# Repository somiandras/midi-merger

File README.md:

# Midi Merge Box

My embedded 🦀 Rust learning project: 2 in, 5 out MIDI merge box based
on a Raspberry Pico board.

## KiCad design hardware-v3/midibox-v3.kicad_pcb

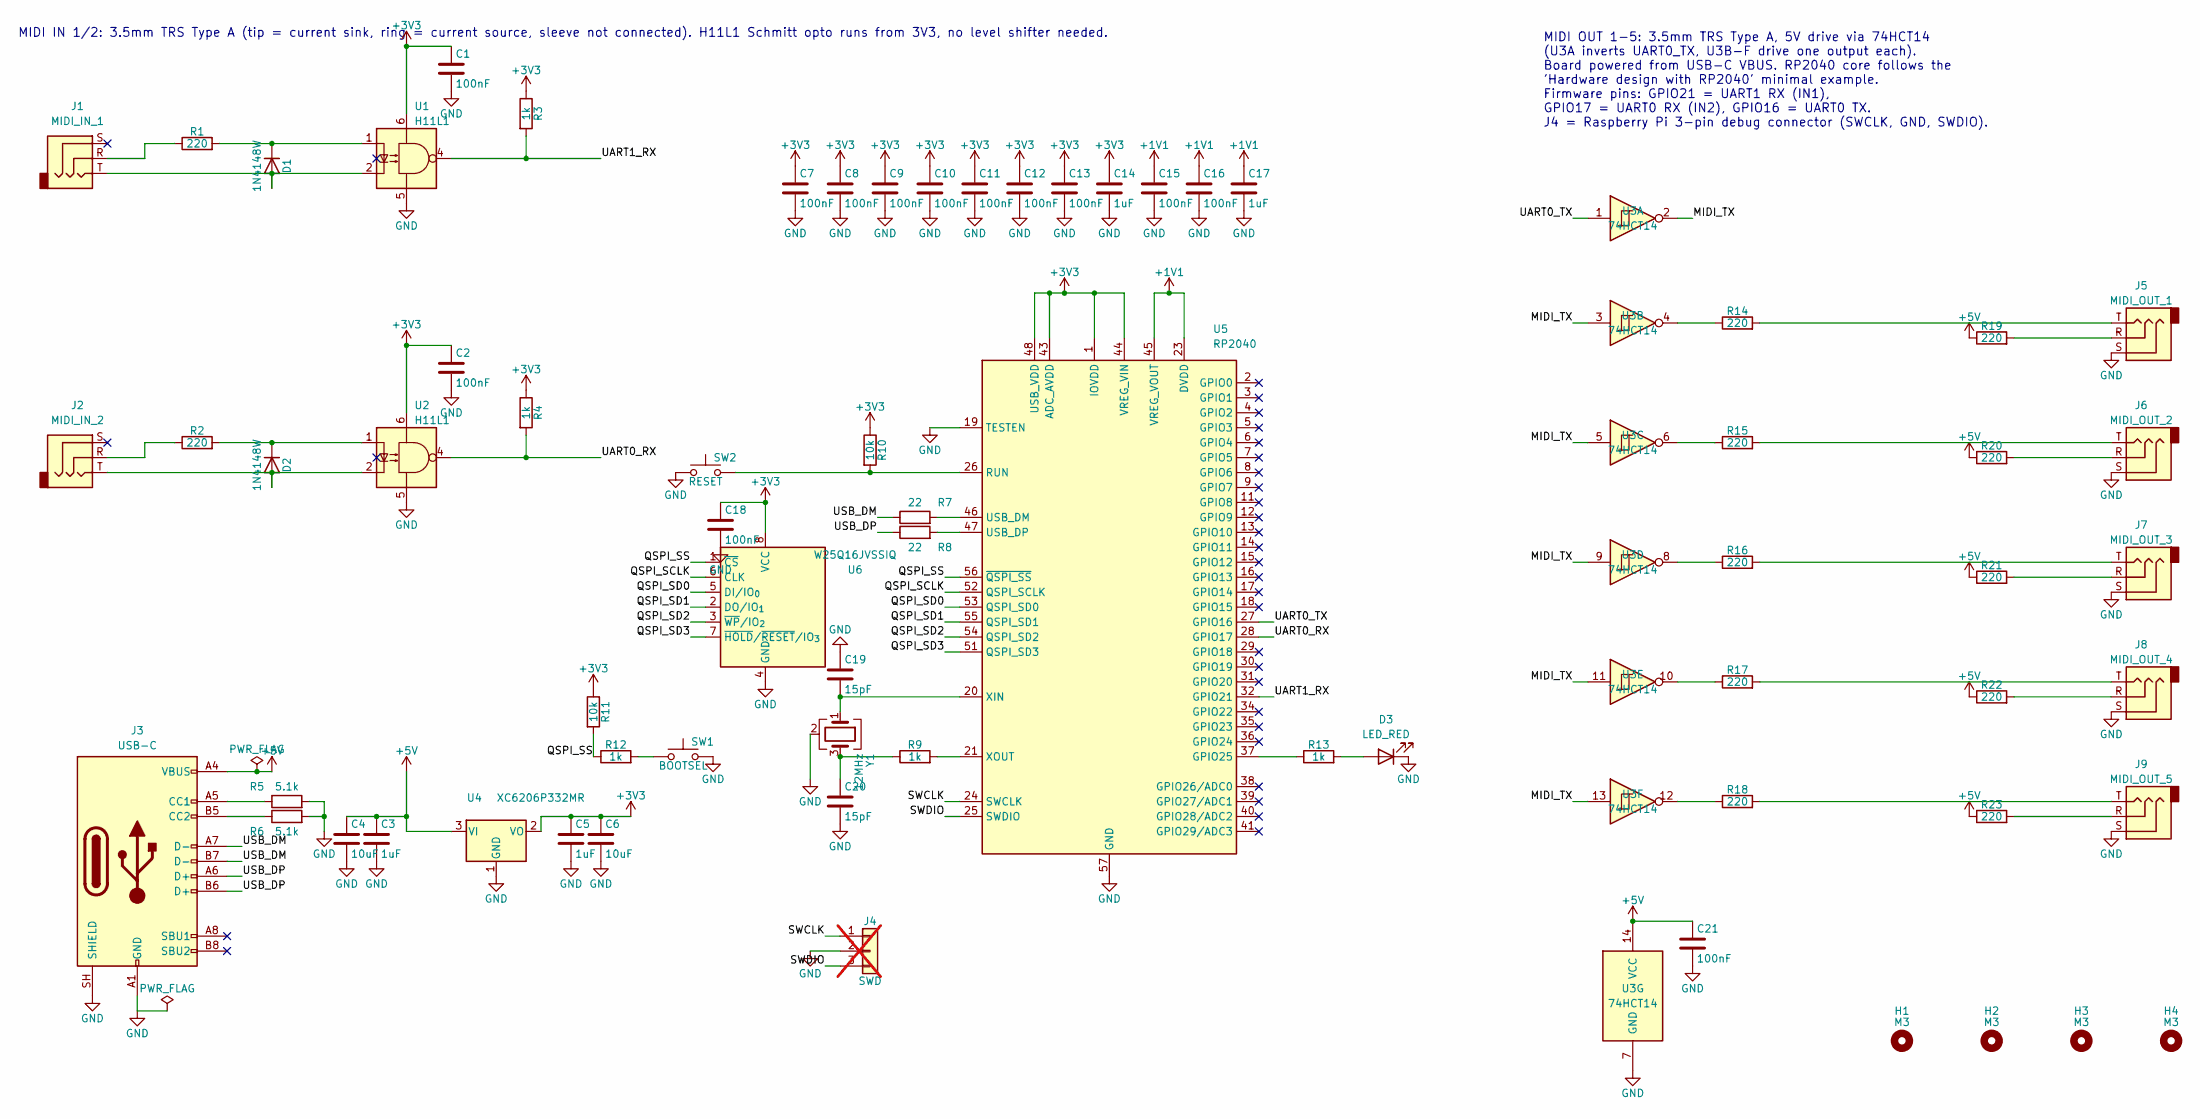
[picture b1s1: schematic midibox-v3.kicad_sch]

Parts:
C1, C2, C7, C8, C9, C10, C11, C12, C13, C15, C16, C18, C21: 100nF; C_0402_1005Metric; LCSC C1525
C3, C5, C14, C17: 1uF; C_0402_1005Metric; LCSC C52923
C4, C6: 10uF; C_0805_2012Metric; LCSC C15850
C19, C20: 15pF; C_0402_1005Metric; LCSC C1548
D1, D2: 1N4148W; D_SOD-123; LCSC C81598
D3: LED_RED; LED_0603_1608Metric; MPN KT-0603R; LCSC C2286
H1, H2, H3, H4: M3; MountingHole_3.2mm_M3
J1: MIDI_IN_1; PJ-3136-B_TRS; MPN PJ-3136-B
J2: MIDI_IN_2; PJ-3136-B_TRS; MPN PJ-3136-B
J3: USB-C; USB_C_Receptacle_HRO_TYPE-C-31-M-12; MPN TYPE-C-31-M-12; LCSC C165948
J4: SWD; PinHeader_1x03_P2.54mm_Vertical; not fitted
J5: MIDI_OUT_1; PJ-3136-B_TRS; MPN PJ-3136-B
J6: MIDI_OUT_2; PJ-3136-B_TRS; MPN PJ-3136-B
J7: MIDI_OUT_3; PJ-3136-B_TRS; MPN PJ-3136-B
J8: MIDI_OUT_4; PJ-3136-B_TRS; MPN PJ-3136-B
J9: MIDI_OUT_5; PJ-3136-B_TRS; MPN PJ-3136-B
R1, R2, R14, R15, R16, R17, R18, R19, R20, R21, R22, R23: 220; R_0402_1005Metric; LCSC C25091
R3, R4, R9, R12, R13: 1k; R_0402_1005Metric; LCSC C11702
R5, R6: 5.1k; R_0402_1005Metric; LCSC C25905
R7, R8: 22; R_0402_1005Metric; LCSC C25092
R10, R11: 10k; R_0402_1005Metric; LCSC C25744
SW1: BOOTSEL; SW_Push_1P1T_XKB_TS-1187A; MPN TS-1187A-B-A-B; LCSC C318884
SW2: RESET; SW_Push_1P1T_XKB_TS-1187A; MPN TS-1187A-B-A-B; LCSC C318884
U1, U2: H11L1; SMDIP-6_W9.53mm; MPN H11L1SR2M; LCSC C20082
U3: 74HCT14; SOIC-14_3.9x8.7mm_P1.27mm; MPN SN74HCT14DR; LCSC C6769
U4: XC6206P332MR; SOT-23-3; MPN XC6206P332MR-G; LCSC C5446
U5: RP2040; QFN-56-1EP_7x7mm_P0.4mm_EP3.2x3.2mm; MPN RP2040; LCSC C2040
U6: W25Q16JVSSIQ; SOIC-8_5.3x5.3mm_P1.27mm; MPN W25Q16JVSSIQ; LCSC C131025
Y1: 12MHz; Crystal_SMD_3225-4Pin_3.2x2.5mm; MPN ABM8-272-T3; LCSC C20625731

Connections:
+1V1: C15.1, C16.1, C17.1, U5.23 (DVDD), U5.45 (VREG_VOUT), U5.50 (DVDD)
+3V3: C1.1, C2.1, C5.1, C6.1, C7.1, C8.1, C9.1, C10.1, C11.1, C12.1, C13.1, C14.1, C18.1, R3.1, R4.1, R10.1, R11.1, U1.6, U2.6, U4.2 (VO), U5.1 (IOVDD), U5.10 (IOVDD), U5.22 (IOVDD), U5.33 (IOVDD), U5.42 (IOVDD), U5.43 (ADC_AVDD), U5.44 (VREG_VIN), U5.48 (USB_VDD), U5.49 (IOVDD), U6.8 (VCC)
+5V: C3.1, C4.1, C21.1, J3.A4 (VBUS), J3.A9 (VBUS), J3.B4 (VBUS), J3.B9 (VBUS), R19.1, R20.1, R21.1, R22.1, R23.1, U3.14 (VCC), U4.3 (VI)
/MIDI_TX: U3.2, U3.3, U3.5, U3.9, U3.11, U3.13
/QSPI_SCLK: U5.52 (QSPI_SCLK), U6.6 (CLK)
/QSPI_SD0: U5.53 (QSPI_SD0), U6.5 (DI/IO_{0})
/QSPI_SD1: U5.55 (QSPI_SD1), U6.2 (DO/IO_{1})
/QSPI_SD2: U5.54 (QSPI_SD2), U6.3 (~WP/IO_{2})
/QSPI_SD3: U5.51 (QSPI_SD3), U6.7 (~HOLD/~RESET/IO_{3})
/QSPI_SS: R11.2, R12.1, U5.56 (~QSPI_SS), U6.1 (~CS)
/SWCLK: J4.1, U5.24 (SWCLK)
/SWDIO: J4.3, U5.25 (SWDIO)
/UART0_RX: R4.2, U2.4, U5.28 (GPIO17)
/UART0_TX: U3.1, U5.27 (GPIO16)
/UART1_RX: R3.2, U1.4, U5.32 (GPIO21)
/USB_DM: J3.A7 (D-), J3.B7 (D-), R7.1
/USB_DP: J3.A6 (D+), J3.B6 (D+), R8.1
GND: C1.2, C2.2, C3.2, C4.2, C5.2, C6.2, C7.2, C8.2, C9.2, C10.2, C11.2, C12.2, C13.2, C14.2, C15.2, C16.2, C17.2, C18.2, C19.1, C20.2, C21.2, D3.1 (K), J3.A1 (GND), J3.A12 (GND), J3.B1 (GND), J3.B12 (GND), J3.SH (SHIELD), J4.2, J5.S, J6.S, J7.S, J8.S, J9.S, R5.2, R6.2, SW1.2, SW2.1, U1.5, U2.5, U3.7 (GND), U4.1 (GND), U5.19 (TESTEN), U5.57 (GND), U6.4 (GND), Y1.2 (G), Y1.4 (G)
unnamed: C20.1, R9.1, Y1.3
unnamed: D1.2 (A), J1.T, U1.2
unnamed: D1.1 (K), R1.2, U1.1
unnamed: D2.2 (A), J2.T, U2.2
unnamed: D2.1 (K), R2.2, U2.1
unnamed: D3.2 (A), R13.2
unnamed: J1.R, R1.1
unnamed: J2.R, R2.1
unnamed: J3.A5 (CC1), R5.1
unnamed: J3.B5 (CC2), R6.1
unnamed: J5.R, R19.2
unnamed: J5.T, R14.2
unnamed: J6.R, R20.2
unnamed: J6.T, R15.2
unnamed: J7.R, R21.2
unnamed: J7.T, R16.2
unnamed: J8.R, R22.2
unnamed: J8.T, R17.2
unnamed: J9.R, R23.2
unnamed: J9.T, R18.2
unnamed: R12.2, SW1.1
unnamed: R14.1, U3.4
unnamed: R15.1, U3.6
unnamed: R16.1, U3.8
unnamed: R17.1, U3.10
unnamed: R18.1, U3.12
unnamed: R13.1, U5.37 (GPIO25)
unnamed: R10.2, SW2.2, U5.26 (RUN)
unnamed: R7.2, U5.46 (USB_DM)
unnamed: R8.2, U5.47 (USB_DP)
unnamed: C19.2, U5.20 (XIN), Y1.1
unnamed: R9.2, U5.21 (XOUT)

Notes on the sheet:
MIDI IN 1/2: 3.5mm TRS Type A (tip = current sink, ring = current source, sleeve not connected). H11L1 Schmitt opto runs from 3V3, no level shifter needed.
MIDI OUT 1-5: 3.5mm TRS Type A, 5V drive via 74HCT14 (U3A inverts UART0_TX, U3B-F drive one output each). Board powered from USB-C VBUS. RP2040 core follows the 'Hardware design with RP2040' minimal example. Firmware pins: GPIO21 = UART1 RX (IN1), GPIO17 = UART0 RX (IN2), GPIO16 = UART0 TX. J4 = Ra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

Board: 2 copper layers, 69 parts (0 on the bottom side), 50 nets, no tracks yet.

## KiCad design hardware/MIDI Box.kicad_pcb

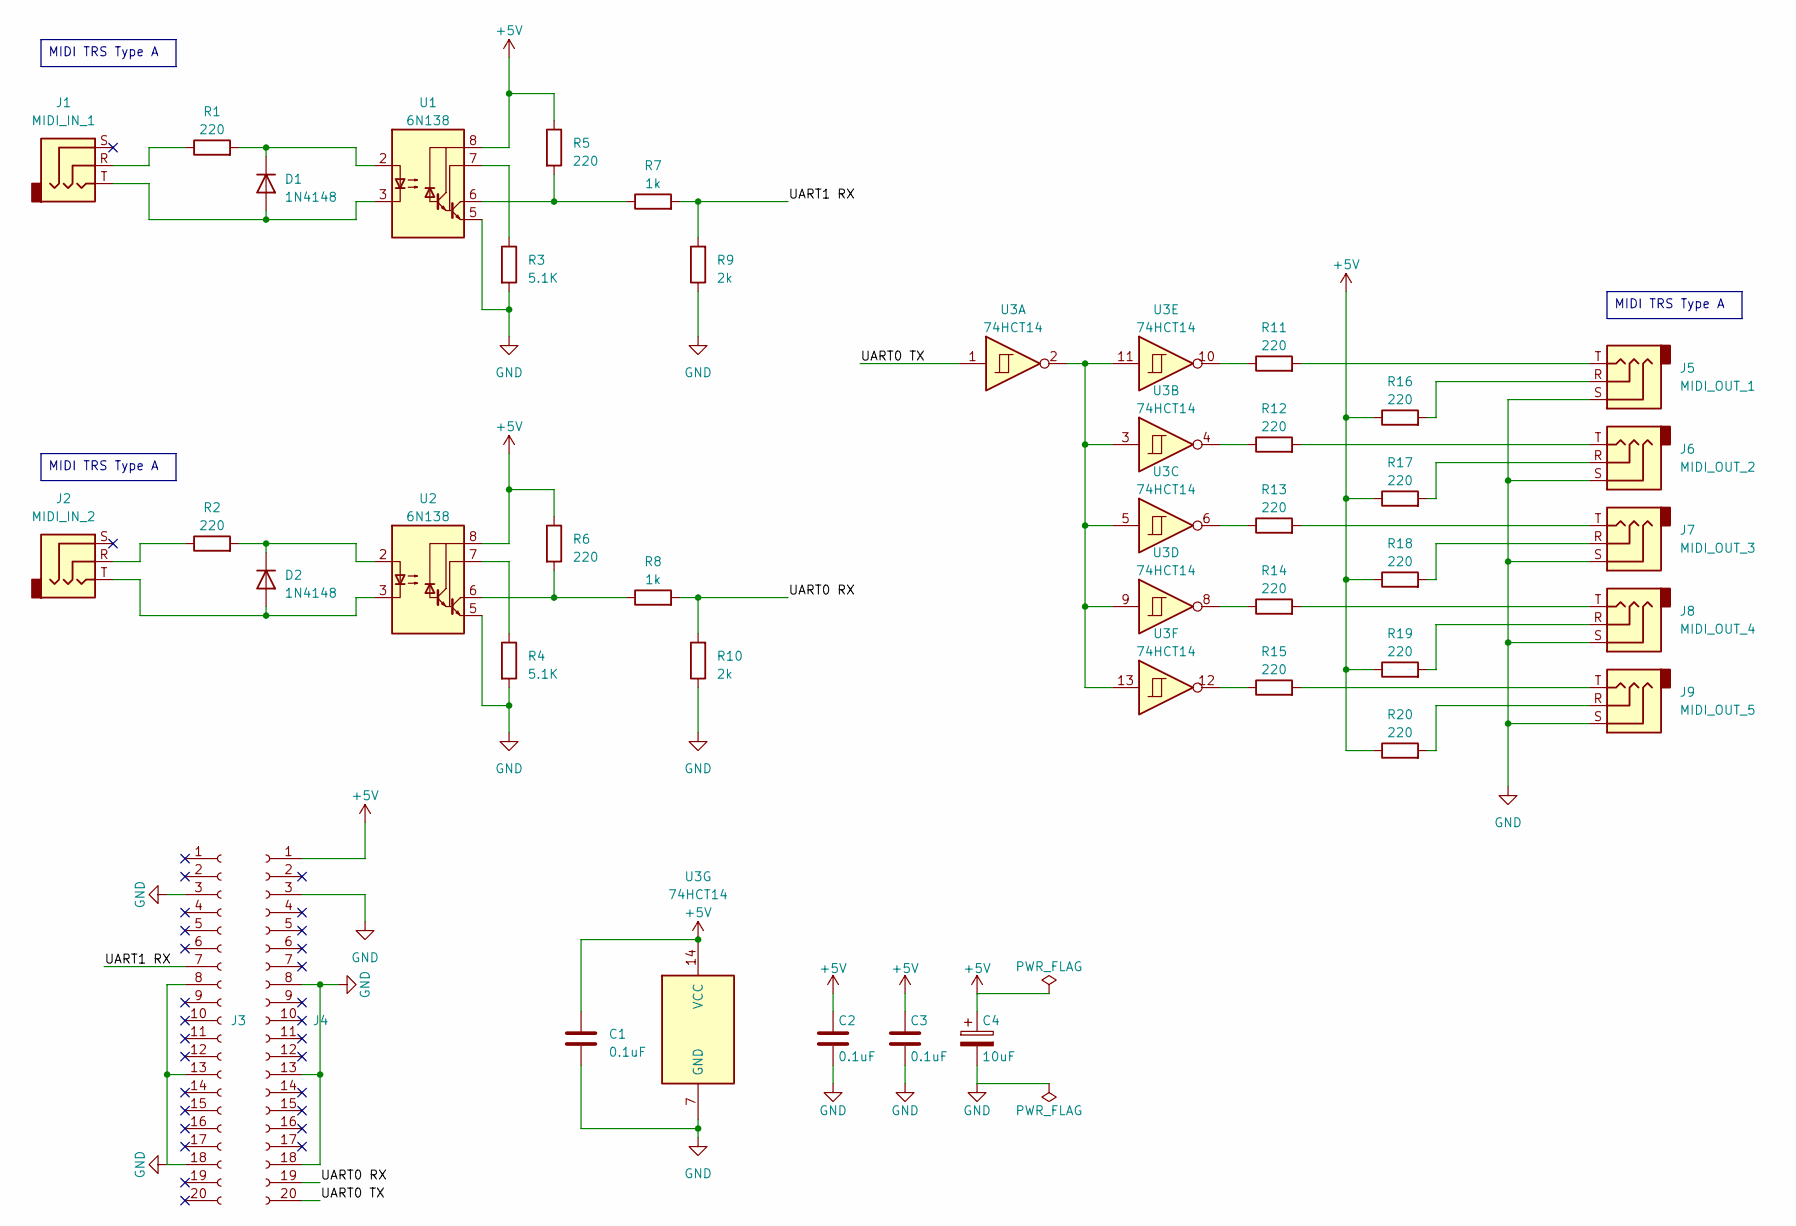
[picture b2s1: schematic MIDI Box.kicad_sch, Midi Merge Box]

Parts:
C1, C2, C3: 0.1uF; C_Disc_D3.4mm_W2.1mm_P2.50mm
C4: 10uF; CP_Radial_D5.0mm_P2.00mm
D1, D2: 1N4148; D_T-1_P5.08mm_Horizontal
J1: MIDI_IN_1; Audio Jack PJ-3136-B
J2: MIDI_IN_2; Audio Jack PJ-3136-B
J3, J4: Conn_01x20_Socket; PinSocket_1x20_P2.54mm_Vertical
J5: MIDI_OUT_1; Audio Jack PJ-3136-B
J6: MIDI_OUT_2; Audio Jack PJ-3136-B
J7: MIDI_OUT_3; Audio Jack PJ-3136-B
J8: MIDI_OUT_4; Audio Jack PJ-3136-B
J9: MIDI_OUT_5; Audio Jack PJ-3136-B
R1, R2, R5, R6, R11, R12, R13, R14, R15, R16, R17, R18, R19, R20: 220; R_Axial_DIN0204_L3.6mm_D1.6mm_P5.08mm_Horizontal
R3, R4: 5.1K; R_Axial_DIN0204_L3.6mm_D1.6mm_P5.08mm_Horizontal
R7, R8: 1k; R_Axial_DIN0204_L3.6mm_D1.6mm_P5.08mm_Horizontal
R9, R10: 2k; R_Axial_DIN0204_L3.6mm_D1.6mm_P5.08mm_Horizontal
U1, U2: 6N138; DIP-8_W7.62mm_Socket
U3: 74HCT14; DIP-14_W7.62mm_Socket

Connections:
+5V: C1.1, C2.1, C3.1, C4.1, J4.1, R5.1, R6.1, R16.1, R17.1, R18.1, R19.1, R20.1, U1.8 (VCC), U2.8 (VCC), U3.14 (VCC)
/UART0 RX: J4.19, R8.2, R10.2
/UART0 TX: J4.20, U3.1
/UART1 RX: J3.7, R7.2, R9.2
GND: C1.2, C2.2, C3.2, C4.2, J3.3, J3.8, J3.13, J3.18, J4.3, J4.8, J4.13, J4.18, J5.S, J6.S, J7.S, J8.S, J9.S, R3.2, R4.2, R9.1, R10.1, U1.5 (GND), U2.5 (GND), U3.7 (GND)
unnamed: D1.2 (A), J1.T, U1.3 (C2)
unnamed: D1.1 (K), R1.2, U1.2 (C1)
unnamed: D2.2 (A), J2.T, U2.3 (C2)
unnamed: D2.1 (K), R2.2, U2.2 (C1)
unnamed: J1.R, R1.1
unnamed: J2.R, R2.1
unnamed: J5.R, R16.2
unnamed: J5.T, R11.2
unnamed: J6.R, R17.2
unnamed: J6.T, R12.2
unnamed: J7.R, R18.2
unnamed: J7.T, R13.2
unnamed: J8.R, R19.2
unnamed: J8.T, R14.2
unnamed: J9.R, R20.2
unnamed: J9.T, R15.2
unnamed: R11.1, U3.10
unnamed: R12.1, U3.4
unnamed: R13.1, U3.6
unnamed: R14.1, U3.8
unnamed: R15.1, U3.12
unnamed: R3.1, U1.7 (VO1)
unnamed: R5.2, R7.1, U1.6 (VO2)
unnamed: R4.1, U2.7 (VO1)
unnamed: R6.2, R8.1, U2.6 (VO2)
unnamed: U3.2, U3.3, U3.5, U3.9, U3.11, U3.13

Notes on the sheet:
MIDI TRS Type A

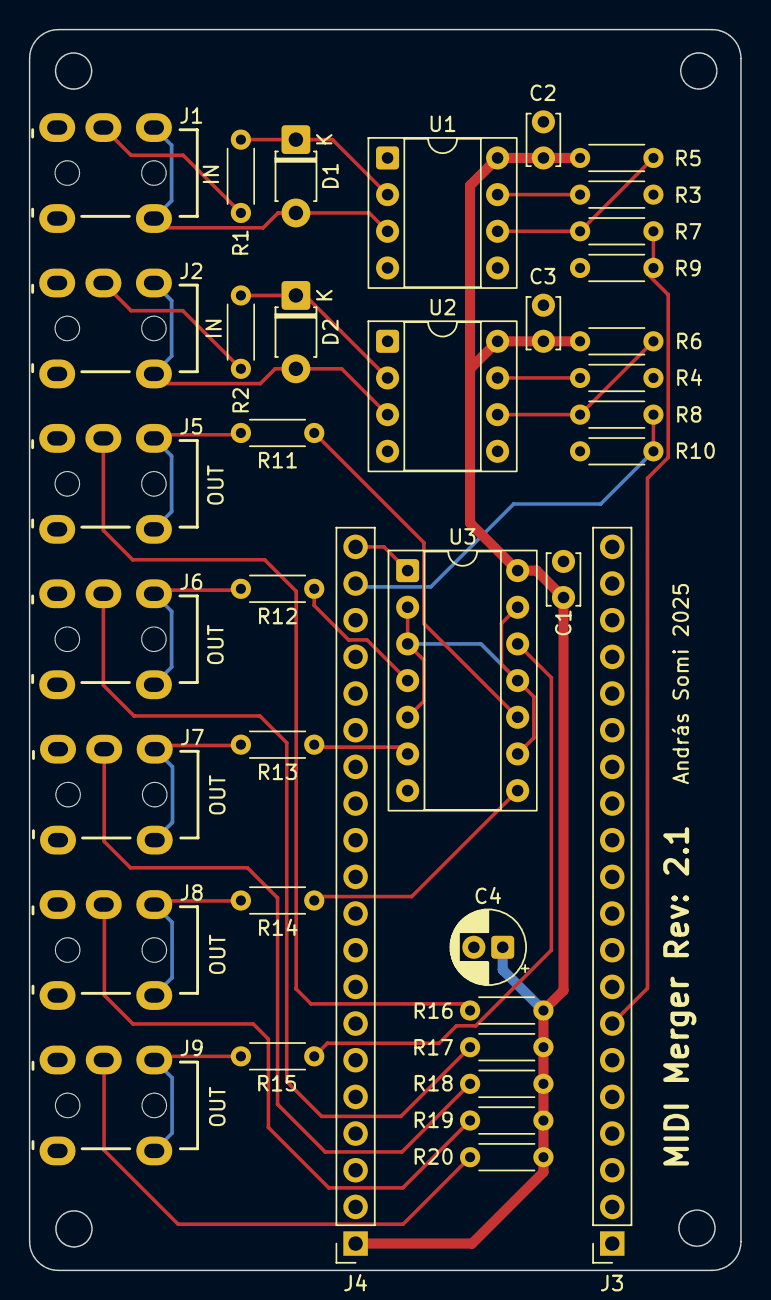
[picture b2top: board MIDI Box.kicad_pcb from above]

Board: 2 copper layers, 49.3 x 85.9 mm, 38 parts (0 on the bottom side), 31 nets.

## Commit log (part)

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2025-01-06 add midi uart srtuct
2025-01-06 add midi generator script
2025-01-06 fix uart pin
2025-01-06 add uart write
2025-01-06 add midiparser
2025-01-06 initial setup
2025-01-06 working tasks
2025-01-06 add basic readme
2025-01-06 reorganize project
2025-01-06 add back Cargo.lock
2025-01-06 add hardware related files
2025-01-12 update gitignore
2025-01-12 update ignore
2025-01-12 remove fab related artifacts
2025-02-13 v2.0 board with TRS sockets
2025-02-16 fix package name
2025-02-16 fix running status errors
2025-03-09 refine error handling
2025-10-01 update dependencies and improve MIDI message handling
2025-10-02 Add CLAUDE.md and CODE_REVIEW_ISSUSES.md
2025-10-02 style: format code for improved readability and consistency
2025-10-03 style: improve code formatting for better readability
2025-10-04 feat: add local settings configuration and update .gitignore for project management files
